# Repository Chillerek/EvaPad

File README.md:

# Evapad

Evapad is a compact 4-key macropad with an EC11 rotary encoder powered by the Seeed Studio XIAO RP2040.

## Features
* **4-Key Layout:**
* **EC11 Rotary Encoder:**
* **Dual-Layer Case:** 
* **XIAO RP2040 Powered:**

## CAD Model

## PCB
Designed from scratch in KiCad.

## Firmware Overview
Configured for flexible layout changes QMK:
* **Rotary Encoder:** Rotates for volume control, press down to toggle mute.
* **4 Keys:** Mapped to custom shortcuts and macro actions.

## BOM (Bill of Materials)

Here is everything you need to build the Evapad:
* 4x Cherry MX (or compatible) Switches
* 4x Keycaps
* 4x Heatset Inserts
* 4x Bolts
* 1x EC11 Rotary Encoder
* 1x Seeed Studio XIAO RP2040
* 1x Custom Case (2-layer design)

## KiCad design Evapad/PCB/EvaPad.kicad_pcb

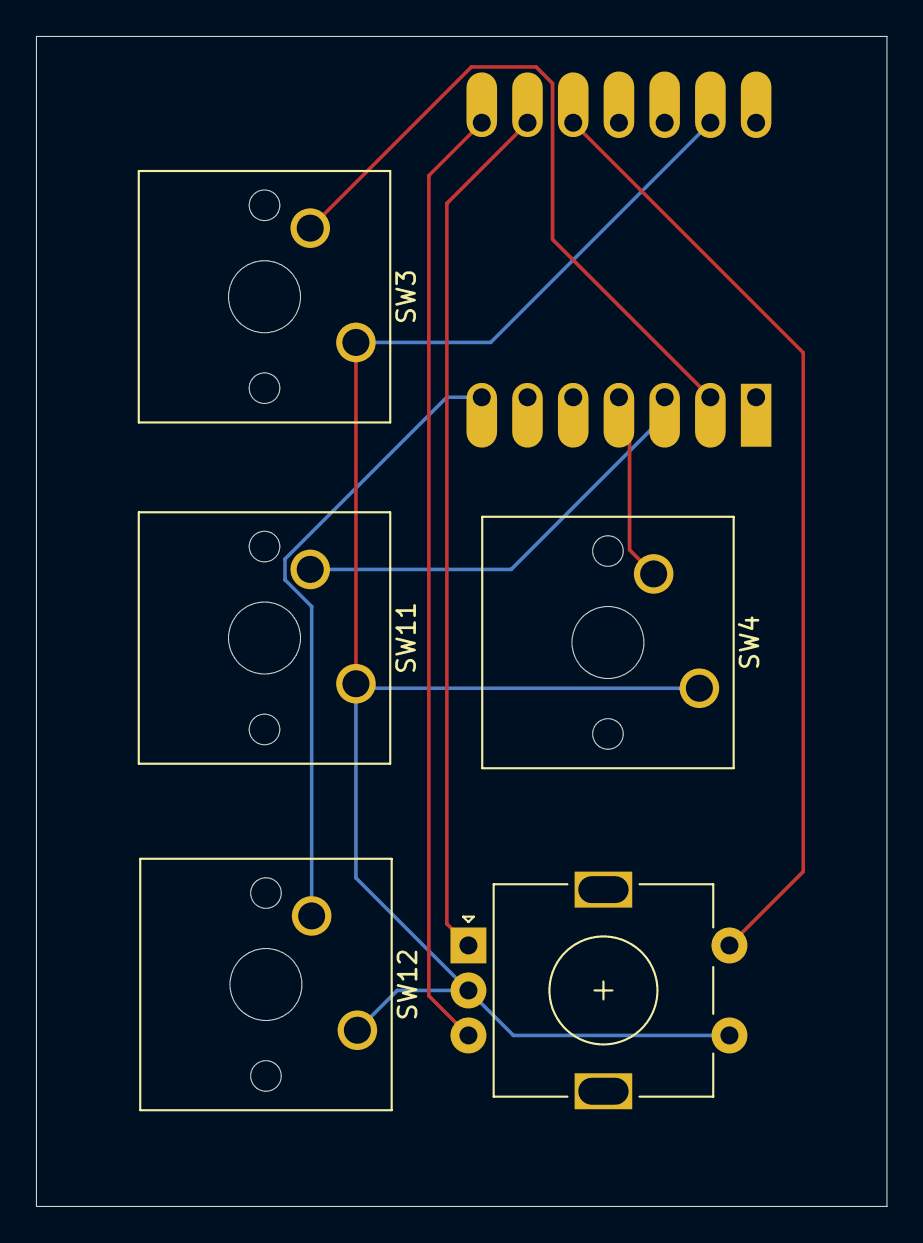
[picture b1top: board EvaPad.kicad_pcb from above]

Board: 2 copper layers, 47.2 x 65.0 mm, 6 parts (1 on the bottom side), 8 nets.

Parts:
SW1: RotaryEncoder_Switch; RotaryEncoder_Alps_EC11E-Switch_Vertical_H20mm
SW3, SW4, SW11, SW12: SW_Push; SW_Cherry_MX_1.00u_PCB
U1: MOUDLE-SEEEDUINO-XIAO; XIAO-Generic-Hybrid-14P-2.54-21X17.8MM

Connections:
GND: SW1.C, SW1.S1, SW3.1, SW4.1, SW11.1, SW12.1, U1.13 (GND)
unnamed: SW3.2, U1.2 (PA4_A1_D1)
unnamed: SW1.S2, U1.10 (PA5_A9_D9_MISO)
unnamed: SW1.A, U1.9 (PA7_A8_D8_SCK)
unnamed: SW11.2, U1.3 (PA10_A2_D2)
unnamed: SW4.2, U1.4 (PA11_A3_D3)
unnamed: SW12.2, U1.7 (PB08_A6_D6_TX)
unnamed: SW1.B, U1.8 (PB09_A7_D7_RX)
